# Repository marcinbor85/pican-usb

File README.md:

# pican-usb
Open-Hardware CAN-USB interface with optoisolation

## Features
- linux SOCKETCAN driver compatible (slcan)
- CANBUS side optoisolation (ISO1050 based)
- powered by USB (build-in DC/DC converter)
- hardware CAN and USB fifo buffers (8-deep CAN and 256-deep USB)
- virtual serial port (FT245 based)
- switchable build-in CAN terminal-resistor (symmetrical)
- up to 1Mbit throughput (no serial port bottleneck)
- EMC and ESD protection (both CAN and USB side)

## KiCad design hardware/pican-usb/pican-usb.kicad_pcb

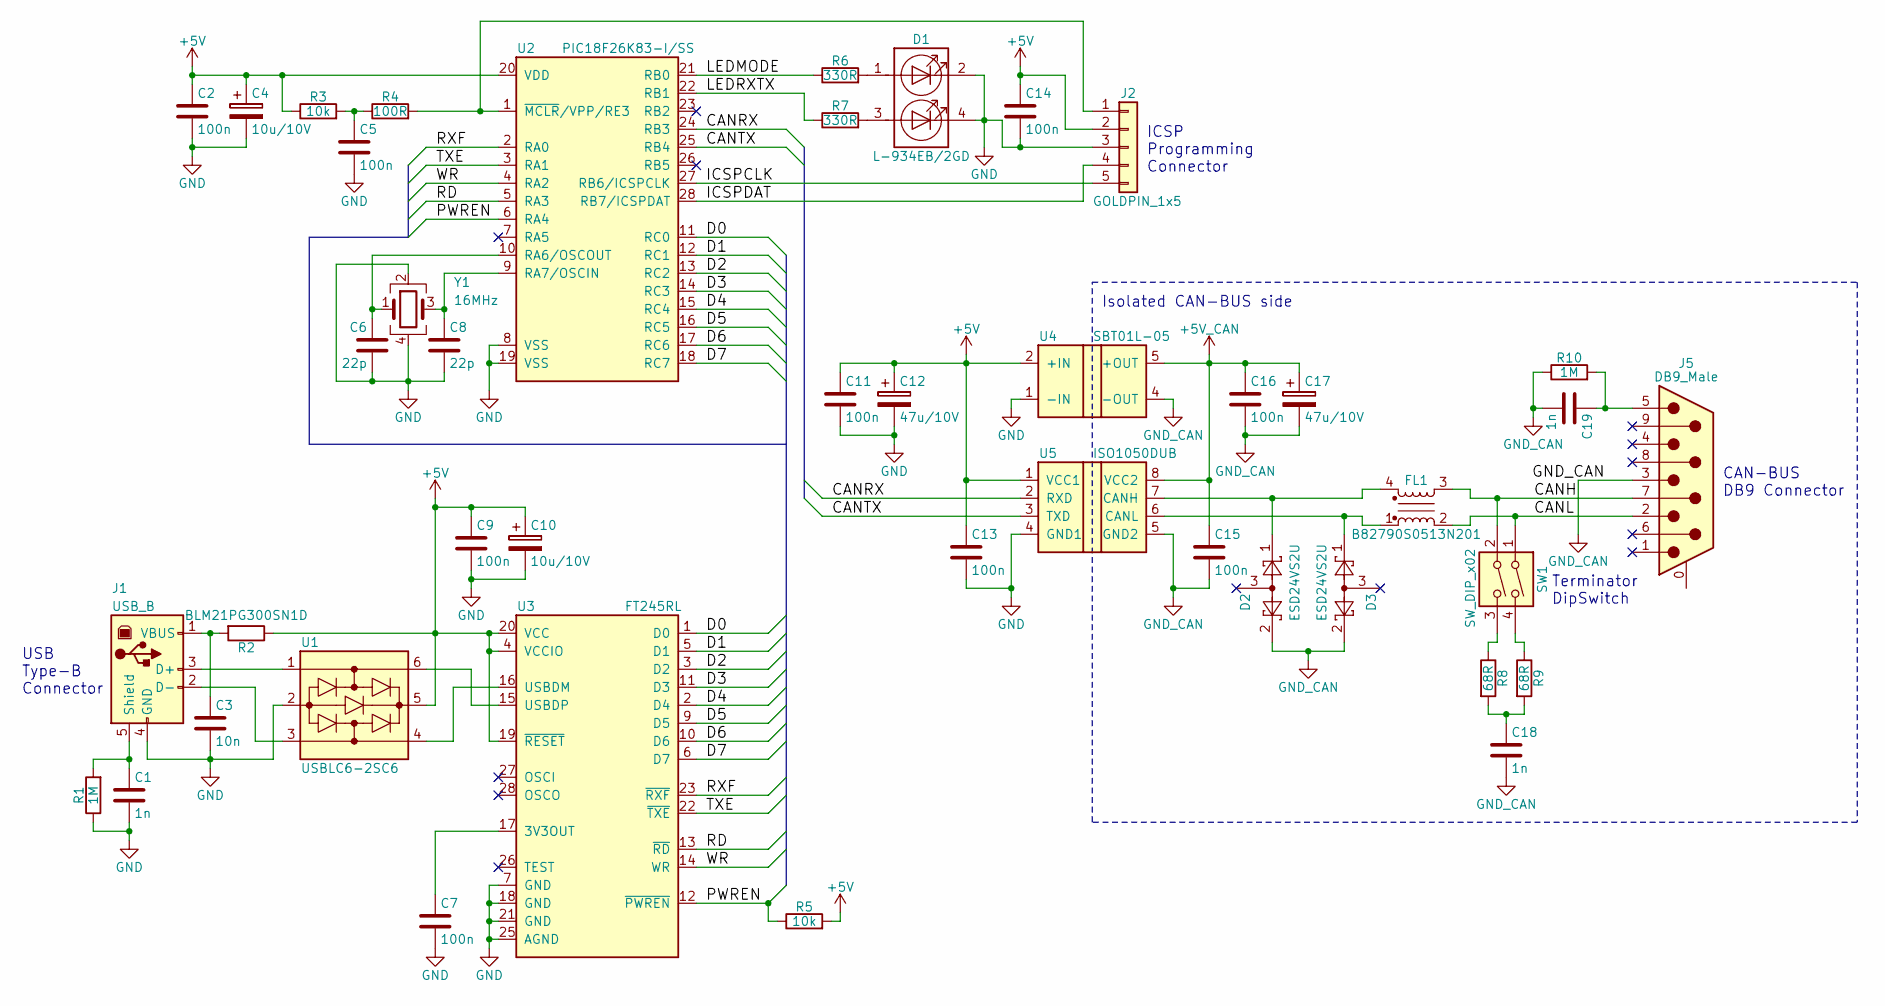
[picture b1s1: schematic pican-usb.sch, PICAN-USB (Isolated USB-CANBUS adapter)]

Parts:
C1, C18, C19: 1n; C_0805
C2, C5, C7, C9, C11, C13, C14, C15, C16: 100n; C_0805
C3: 10n; C_0805
C4, C10: 10u/10V; CP_Tantalum_Case-A_EIA-3216-18_Reflow
C6, C8: 22p; C_0805
C12, C17: 47u/10V; CP_Tantalum_Case-B_EIA-3528-21_Reflow
D1: L-934EB/2GD; L-934EB2
D2, D3: ESD24VS2U; SOT-23
FL1: B82790S0513N201; B82790
J1: USB_B
J2: GOLDPIN_1x5; Pin_Header_Straight_1x05_Pitch2.54mm
J5: DB9_Male; DSUB-9_Male_Horizontal_Pitch2.77x2.84mm_EdgePinOffset7.70mm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
R1, R10: 1M; R_0805
R2: BLM21PG300SN1D; R_0805
R3, R5: 10k; R_0805
R4: 100R; R_0805
R6, R7: 330R; R_0805
R8, R9: 68R; R_1206
SW1: SW_DIP_x02; SW_DIP_x2_W7.62mm_Piano
U1: USBLC6-2SC6; SOT-23-6
U2: PIC18F26K83-I/SS; SSOP-28_5.3x10.2mm_Pitch0.65mm
U3: FT245RL; SSOP-28_5.3x10.2mm_Pitch0.65mm
U4: SBT01L-05; SBT01
U5: ISO1050DUB
Y1: 16MHz; Crystal_SMD_3225-4pin_3.2x2.5mm

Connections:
+5V: C2.1, C4.1, C9.1, C10.1, C11.1, C12.1, C13.1, C14.1, J2.2, R2.1, R3.1, R5.2, U1.5, U2.20 (VDD), U3.4 (VCCIO), U3.19 (~RESET), U3.20 (VCC), U4.2 (+IN), U5.1 (VCC1)
+5V_CAN: C15.1, C16.1, C17.1, U4.5 (+OUT), U5.8 (VCC2)
/CANH: FL1.3, J5.7, SW1.2
/CANL: FL1.2, J5.2, SW1.1
/CANRX: U2.24 (RB3), U5.2 (RXD)
/CANTX: U2.25 (RB4), U5.3 (TXD)
/D0: U2.11 (RC0), U3.1 (D0)
/D1: U2.12 (RC1), U3.5 (D1)
/D2: U2.13 (RC2), U3.3 (D2)
/D3: U2.14 (RC3), U3.11 (D3)
/D4: U2.15 (RC4), U3.2 (D4)
/D5: U2.16 (RC5), U3.9 (D5)
/D6: U2.17 (RC6), U3.10 (D6)
/D7: U2.18 (RC7), U3.6 (D7)
/ICSPCLK: J2.5, U2.27 (RB6/ICSPCLK)
/ICSPDAT: J2.4, U2.28 (RB7/ICSPDAT)
/LEDMODE: R6.1, U2.21 (RB0)
/LEDRXTX: R7.1, U2.22 (RB1)
/PWREN: R5.1, U2.6 (RA4), U3.12 (~PWREN)
/RD: U2.5 (RA3), U3.13 (~RD)
/RXF: U2.2 (RA0), U3.23 (~RXF)
/TXE: U2.3 (RA1), U3.22 (~TXE)
/WR: U2.4 (RA2), U3.14 (WR)
GND: C1.2, C2.2, C3.2, C4.2, C5.2, C6.2, C7.2, C8.2, C9.2, C10.2, C11.2, C12.2, C13.2, C14.2, D1.2 (K1), D1.4 (K2), J1.4 (GND), J2.3, R1.1, U1.2, U2.8 (VSS), U2.19 (VSS), U3.7 (GND), U3.18 (GND), U3.21 (GND), U3.25 (AGND), U4.1 (-IN), U5.4 (GND1), Y1.2, Y1.4
GND_CAN: C15.2, C16.2, C17.2, C18.2, C19.2, D2.2, D3.2, J5.3, R10.1, U4.4 (-OUT), U5.5 (GND2)
unnamed: C1.1, J1.5 (Shield), R1.2
unnamed: C3.1, J1.1 (VBUS), R2.2
unnamed: C5.1, R3.2, R4.1
unnamed: C6.1, U2.10 (RA6/OSCOUT), Y1.1
unnamed: C7.1, U3.17 (3V3OUT)
unnamed: C8.1, U2.9 (RA7/OSCIN), Y1.3
unnamed: C18.1, R8.2, R9.2
unnamed: C19.1, J5.5, R10.2
unnamed: D1.1 (A1), R6.2
unnamed: D1.3 (A2), R7.2
unnamed: D2.1, FL1.4, U5.7 (CANH)
unnamed: D3.1, FL1.1, U5.6 (CANL)
unnamed: J1.2 (D-), U1.3
unnamed: J1.3 (D+), U1.1
unnamed: J2.1, R4.2, U2.1 (~MCLR~/VPP/RE3)
unnamed: R8.1, SW1.3
unnamed: R9.1, SW1.4
unnamed: U1.4, U3.16 (USBDM)
unnamed: U1.6, U3.15 (USBDP)

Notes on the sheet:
ICSP Programming Connector
CAN-BUS DB9 Connector
USB Type-B Connector
Terminator DipSwitch
Isolated CAN-BUS side

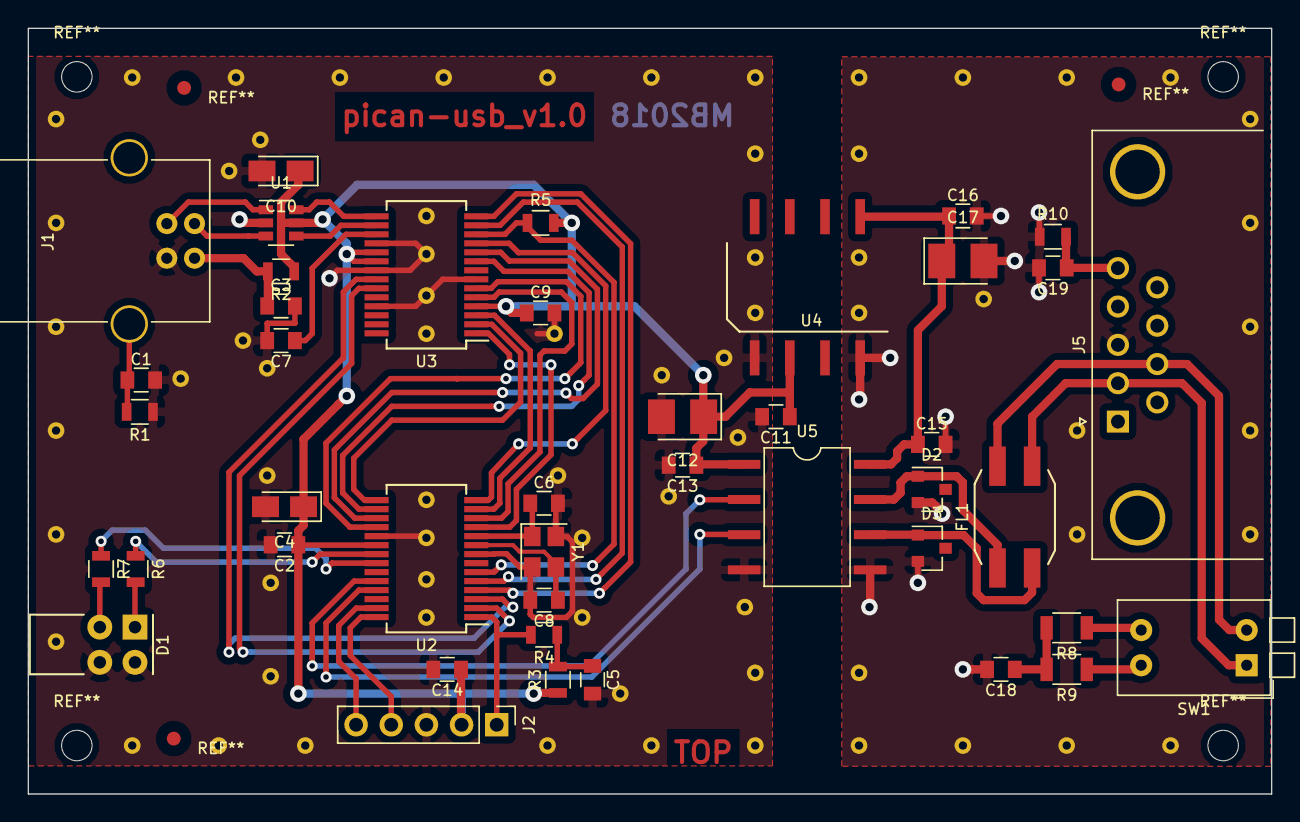
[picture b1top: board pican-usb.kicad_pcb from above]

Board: 2 copper layers, 89.8 x 55.3 mm, 43 parts (0 on the bottom side), 44 nets.

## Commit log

2018-03-25 first full working version
2018-03-25 dodane pliki kicad'a
2018-03-25 readme
    simple description
2018-03-25 license file added
2018-03-25 photo added
2018-03-25 update readme
    photo added
2018-03-28 przeniesiona obsługa potwierdzeń slcan z app do slcan
2018-03-28 refaktoring
